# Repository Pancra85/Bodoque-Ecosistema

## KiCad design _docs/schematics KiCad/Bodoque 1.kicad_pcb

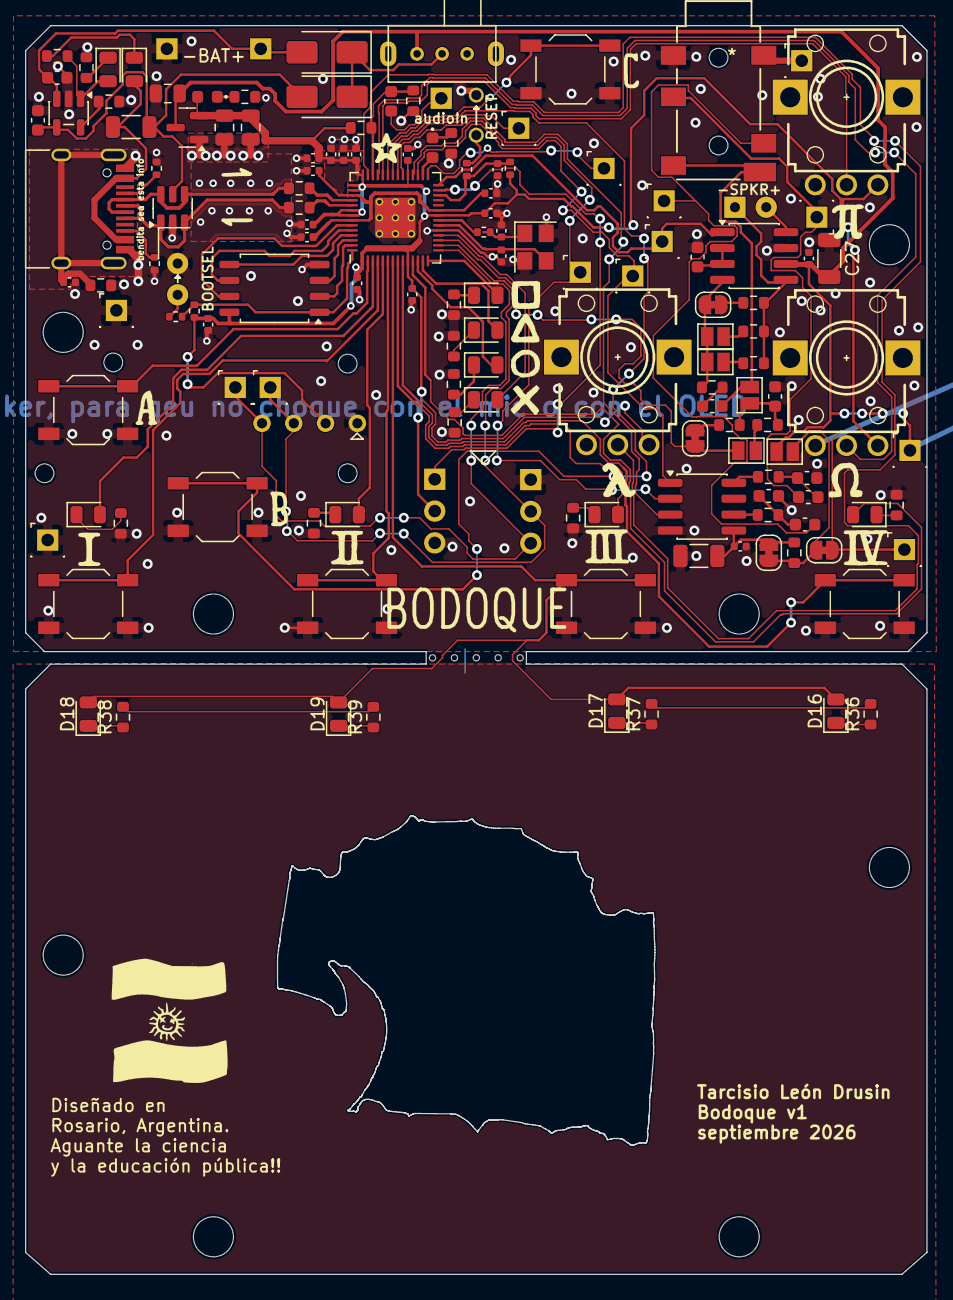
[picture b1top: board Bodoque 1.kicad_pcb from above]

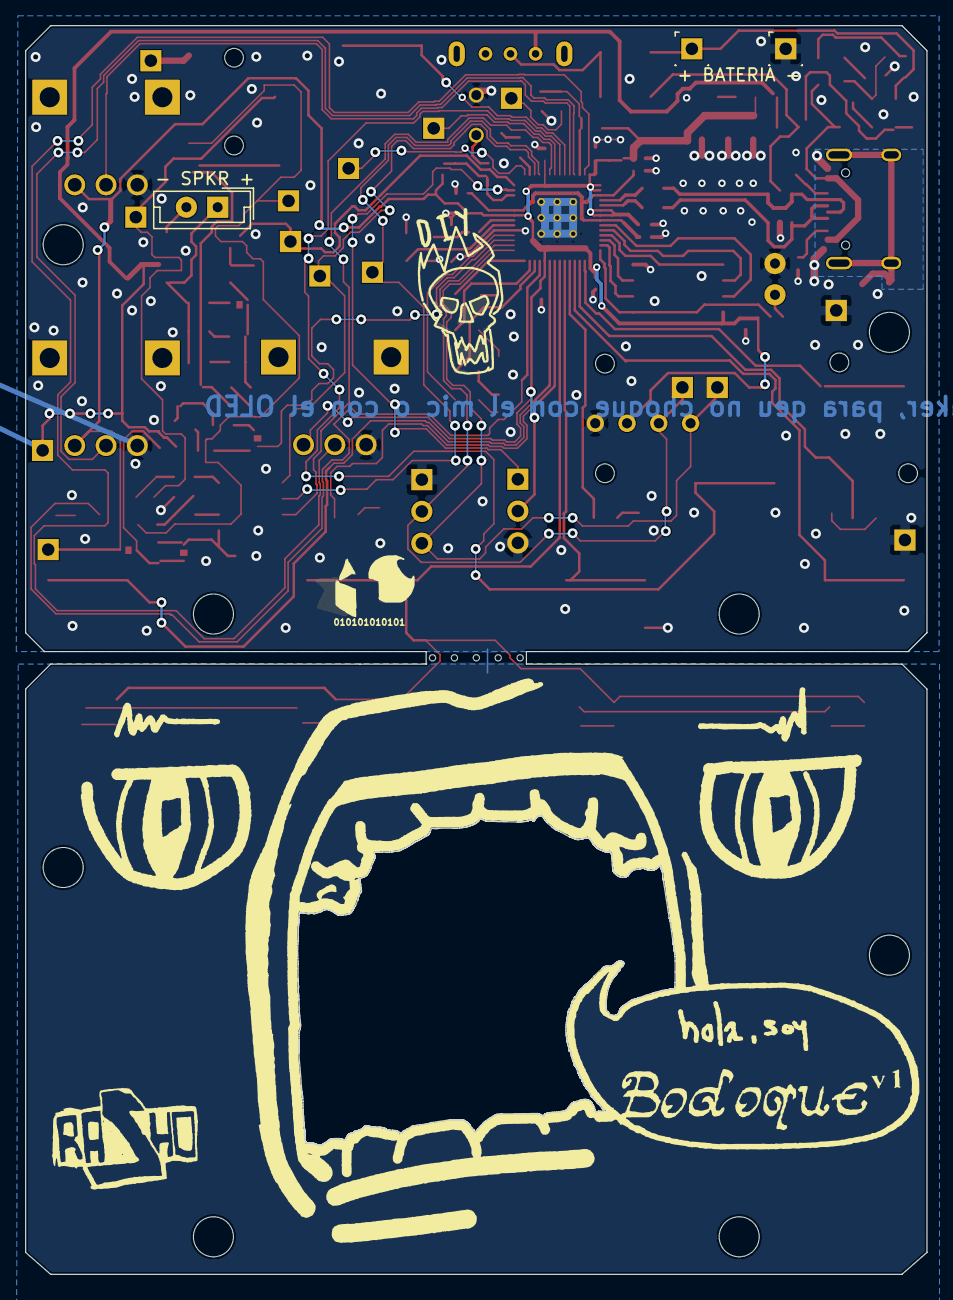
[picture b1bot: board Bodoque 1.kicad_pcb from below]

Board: 2 copper layers, 72.0 x 99.8 mm, 155 parts (3 on the bottom side), 99 nets.

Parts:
C1, C5, C6, C9, C10, C11, C12, C13, C14, C15, C18, C26, C28, C32: 100n; C_0402_1005Metric
C2, C3: 22pF; C_0402_1005Metric
C4, C8, C19: 1uF; C_0402_1005Metric
C7, C16, C17: 4.7uF; C_0805_2012Metric
C20, C21: 4.7u; C_0603_1608Metric
C22, C34, C35: 10u; C_0603_1608Metric
C24, C25, C29, C36, C37: 100n; C_0603_1608Metric
C27: 100u; C_1206_3216Metric
C33: 47u; C_1206_3216Metric
D1: SRV05-4; SOT-23-6
D2: POWER; LED_0603_1608Metric_Dot
D3, D4, D7, D8, D9, D10, D11, D12, D13, D14, D16, D17, D18, D19: LED; LED_0805_2012Metric
D5, D6: SS14; D_SMA
D15: LED; LED_0603_1608Metric_Dot
H3, H3#2, H3#3, H3#4, H3#5, H3#6, H3#7, H3#8, H3#9, H3#10, H3#11, H3#12: MountingHole; MountingHole_3.2mm_M3_ISO14580
J1: USB_C_Receptacle_USB2.0; USB_C_Receptacle_HRO_TYPE-C-31-M-12
J2: PJ-342 141; PJ-342B-TX-SMT_XKB
JP1, JP2, JP4, JP6, JP12: SolderJumper-2_P1.3mm_Open_Pad1.0x1.5mm
JP3, JP5, JP7: SolderJumper-2_P1.3mm_Bridged_RoundedPad1.0x1.5mm
JP8: CORTAR!; SolderJumper-2_P1.3mm_Bridged_RoundedPad1.0x1.5mm
MIC1: INMP441
OL1: OLED
R1, R7, R9: 1k; R_0402_1005Metric
R2, R11, R15, R17, R18, R19, R23, R24, R28, R29, R35: 4.7k; R_0603_1608Metric
R3, R4, R10, R12: 5k1; R_0402_1005Metric
R5, R6: 22R; R_0603_1608Metric
R8: 0R; R_1206_3216Metric
R13: 3.3k; R_0603_1608Metric
R14: 5.1k; R_0603_1608Metric
R16, R26: 100k; R_0603_1608Metric
R20: 30k; R_0603_1608Metric
R21, R30: 20k; R_0603_1608Metric
R22, R25: 10k; R_0603_1608Metric
R27: 10; R_0603_1608Metric
R31: 270; R_0603_1608Metric
R32, R33: 100; R_0603_1608Metric
R34: 1k; R_0603_1608Metric
R36, R37, R38, R39: 2.2k; R_0603_1608Metric
RV1, RV2, RV3: R_Potentiometer; Alpha 9mm vertical pot
SW1: BOOTSEL; JST_EH_B2B-EH-A_1x02_P2.50mm_Vertical small
SW2: RESET; JST_EH_B2B-EH-A_1x02_P2.50mm_Vertical small
SW3, SW4, SW5, SW6, SW7, SW8, SW9: SW_MEC_5G; SW_SPST_TL3342
SW10: SW_SPDT; SK-12D07 mini Switch
TP1: Bat-; PinHeader_1x01_P2.54mm_Vertical with label
TP2: audioIn; PinHeader_1x01_P2.54mm_Vertical with label
TP3, TP6: GND; PinHeader_1x01_P2.54mm_Vertical with label
TP4: - SPKR +; JST_EH_B2B-EH-A_1x02_P2.50mm_Vertical small
TP5: SD; PinHeader_1x01_P2.54mm_Vertical with label
TP7: VSW; PinHeader_1x01_P2.54mm_Vertical with label
TP8: 3.3V; PinHeader_1x01_P2.54mm_Vertical with label
TP9: SDA; PinHeader_1x01_P2.54mm_Vertical with label
TP10: SCL; PinHeader_1x01_P2.54mm_Vertical with label
TP11: 18; PinHeader_1x01_P2.54mm_Vertical with label
TP12: 23; PinHeader_1x01_P2.54mm_Vertical with label
TP13: dacWS; PinHeader_1x01_P2.54mm_Vertical with label
TP14: dacBCK; PinHeader_1x01_P2.54mm_Vertical with label
TP16: micIn; PinHeader_1x01_P2.54mm_Vertical with label
TP25: Bat+; PinHeader_1x01_P2.54mm_Vertical with label
TP26: DACROut; PinHeader_1x01_P2.54mm_Vertical with label
TP27: DACLOut; PinHeader_1x01_P2.54mm_Vertical with label
U1: W25Q16JVSIQ; SOIC-8_5.23x5.23mm_P1.27mm
U2: RP2040; RP2040-QFN-56
U3: MCP73831-3-OT; SOT-23-5
U4: XC6206PxxxMR; SOT-23
U5: NS8002; SOP-8_3.76x4.96mm_P1.27mm
U6: PT8211; SOP-8_3.76x4.96mm_P1.27mm
X1: 12MHz; Crystal_SMD_3225-4Pin_3.2x2.5mm

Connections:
+1V1: C4.2, C5.1, C6.1, U2.23 (DVDD), U2.45 (VREG_VOUT), U2.50 (DVDD)
+3V3: C1.1, C7.1, C8.1, C9.1, C10.1, C11.1, C12.1, C13.1, C14.1, C15.1, C17.1, C18.1, D2.2, JP3.2 (B), MIC1.2 (VDD), OL1.3 (VCC), R10.2, R12.2, R16.1, RV1.3, RV2.3, RV3.3, TP8.1 (1_1), U1.8 (VCC), U2.1 (IOVDD), U2.10 (IOVDD), U2.22 (IOVDD), U2.33 (IOVDD), U2.42 (IOVDD), U2.43 (ADC_AVDD), U2.44 (VREG_VIN), U2.48 (USB_VDD), U2.49 (IOVDD), U4.2 (VO)
+5V: C20.2, D1.5 (VP), D5.2 (A), R8.2, U3.4 (V_{DD})
+BATT: C21.2, D6.2 (A), TP25.1 (1_1), U3.3 (V_{BAT})
+VSW: C16.1, C26.2, C27.2, JP2.2 (B), SW10.3 (C), TP7.1 (1_1), U4.3 (VI), U5.6 (VCC)
/441SCK: MIC1.6 (SCK), OL1.1 (SDA), TP9.1 (1_1), U2.15 (GPIO12)
/441SD: MIC1.1 (SD), U2.27 (GPIO16)
/441WS: MIC1.5 (WS), OL1.2 (SCL), TP10.1 (1_1), U2.16 (GPIO13)
/CS: R1.1, R12.1, U1.1 (~CS), U2.56 (QSPI_SS_N)
/DACLOut: C35.2, J2.4, TP27.1 (1_1)
/DACLOutSwitch: C24.2, J2.5, J2.6, JP12.2 (B)
/DACROut: C34.2, J2.3, TP26.1 (1_1)
/GPIO0: SW8.1, U2.2 (GPIO0)
/GPIO1: D7.2 (A), U2.3 (GPIO1)
/GPIO2: SW6.1, U2.4 (GPIO2)
/GPIO3: D8.2 (A), U2.5 (GPIO3)
/GPIO4: SW3.1, U2.6 (GPIO4)
/GPIO5: D16.2 (A), D17.2 (A), D18.2 (A), D19.2 (A), SW4.1, U2.7 (GPIO5)
/GPIO6: D9.2 (A), U2.8 (GPIO6)
/GPIO7: SW5.1, U2.9 (GPIO7)
/GPIO8: D10.2 (A), U2.11 (GPIO8)
/GPIO9: D11.2 (A), U2.12 (GPIO9)
/GPIO10: D12.2 (A), U2.13 (GPIO10)
/GPIO11: D13.2 (A), U2.14 (GPIO11)
/GPIO14: JP4.1 (A), JP5.1 (A), U2.17 (GPIO14)
/GPIO15: D14.2 (A), U2.18 (GPIO15)
/GPIO17: TP5.1 (1_1), U2.28 (GPIO17), U5.1 (SD)
/GPIO18: TP11.1 (1_1), U2.29 (GPIO18)
/GPIO19: D15.2, U2.30 (GPIO19)
/GPIO20: TP14.1 (1_1), U2.31 (GPIO20), U6.1 (BCK)
/GPIO21: TP13.1 (1_1), U2.32 (GPIO21), U6.2 (WS)
/GPIO22: U2.34 (GPIO22), U6.3 (DIN)
/GPIO23: TP12.1 (1_1), U2.35 (GPIO23)
/GPIO24: SW9.1, U2.36 (GPIO24)
/GPIO25: SW7.1, U2.37 (GPIO25)
/GPIO26/ADC0: RV1.2, U2.38 (GPIO26/ADC0)
/GPIO27/ADC1: RV2.2, U2.39 (GPIO27/ADC1)
/GPIO28/ADC2: C22.1, R16.2, R26.1, U2.40 (GPIO28/ADC2)
/GPIO29/ADC3: RV3.2, U2.41 (GPIO29/ADC3)
/RP2040/QSPI_CLK: U1.6 (CLK), U2.52 (QSPI_SCLK)
/RP2040/SD0: U1.5 (DI(IO0)), U2.53 (QSPI_SD0)
/RP2040/SD1: U1.2 (DO(IO1)), U2.55 (QSPI_SD1)
/RP2040/SD2: U1.3 (IO2), U2.54 (QSPI_SD2)
/RP2040/SD3: U1.7 (IO3), U2.51 (QSPI_SD3)
/RP2040/USB_DT+: R5.2, U2.47 (D+)
/RP2040/USB_DT-: R6.2, U2.46 (D-)
/USBC/CC1: J1.A5 (CC1), R3.1
/USBC/CC2: J1.B5 (CC2), R4.1
/USB_D+: D1.1 (L1), D1.3 (L2), J1.A6 (D+), J1.B6 (D+), R5.1
/USB_D-: D1.4 (L3), D1.6 (L4), J1.A7 (D-), J1.B7 (D-), R6.1
/~RESET: C19.1, R9.1, R10.1, U2.26 (~RUN)
GND: C1.2, C2.1, C3.1, C4.1, C5.2, C6.2, C7.2, C8.2, C9.2, C10.2, C11.2, C12.2, C13.2, C14.2, C15.2, C16.2, C17.2, C18.2, C19.2, C20.1, C21.1, C25.2, C26.1, C27.1, C28.2, C29.1, C32.1, C33.2, C36.1, C37.1, D1.2 (VN), J1.A1 (GND), J1.A12 (GND), J1.B1 (GND), J1.B12 (GND), J2.1, MIC1.3 (GND), MIC1.4 (L/R), OL1.4 (GND), R2.2, R3.2, R4.2, R11.2, R13.2, R14.1, R17.2, R18.2, R19.2, R23.2, R24.2, R25.2, R26.2, R28.2, R29.2, R35.2, RV1.1, RV2.1, RV3.1, SW1.1, SW2.1, SW3.2, SW4.2, SW5.2, SW6.2, SW7.2, SW8.2, SW9.2, TP1.1 (1_1), TP3.1 (1_1), TP6.1 (1_1), U1.4 (GND), U2.19 (TESTEN), U2.57 (GND), U3.2 (V_{SS}), U4.1 (GND), U5.7 (GND), U6.4 (GND), X1.2, X1.4
unnamed: C3.2, R7.1, X1.1
unnamed: C22.2, TP2.1 (1_1)
unnamed: C24.1, R30.2
unnamed: C34.1, C36.2, R32.1
unnamed: C35.1, C37.2, R33.1
unnamed: D2.1, R2.1
unnamed: D3.2 (A), R15.2, U3.1 (STAT)
unnamed: D3.1 (K), R14.2
unnamed: D4.1 (K), R15.1
unnamed: D5.1 (K), D6.1 (K), SW10.2 (B)
unnamed: D7.1 (K), R18.1
unnamed: D8.1 (K), R19.1
unnamed: D9.1 (K), R23.1
unnamed: D10.1 (K), R24.1
unnamed: D11.1 (K), R11.1
unnamed: D12.1 (K), R28.1
unnamed: D13.1 (K), R29.1
unnamed: D14.1 (K), R17.1
unnamed: D15.1, R35.1
unnamed: D16.1 (K), R36.1
unnamed: D17.1 (K), R37.1
unnamed: D18.1 (K), R38.1
unnamed: D19.1 (K), R39.1
unnamed: C28.1, J1.S1 (SHIELD), R25.1
unnamed: J2.2, TP16.1 (1_1)
unnamed: JP1.1 (A), JP6.1 (A), JP7.1 (A), R30.1, U5.4 (-IN)
unnamed: JP1.2 (B), R22.2
unnamed: JP2.1 (A), JP3.1 (A), JP8.1 (A), R27.2
unnamed: JP4.2 (B), R31.2
unnamed: JP5.2 (B), R34.2
unnamed: JP6.2 (B), R20.2
unnamed: JP7.2 (B), R21.2
unnamed: C32.2, C33.1, JP8.2 (B), R27.1, U6.5 (VCC)
unnamed: C29.2, JP12.1 (A), R31.1, R34.1
unnamed: R1.2, SW1.2
unnamed: R9.2, SW2.2
unnamed: R36.2, R37.2
unnamed: R38.2, R39.2
unnamed: C2.2, U2.20 (XTAL_IN), X1.3
unnamed: R7.2, U2.21 (XTAL_OUT)
unnamed: R13.1, U3.5 (PROG)
unnamed: C25.1, U5.2 (BYP), U5.3 (+IN)
unnamed: R20.1, R21.1, R22.1, TP4.1, U5.5 (VO1)
unnamed: TP4.2, U5.8 (VO2)
unnamed: R33.2, U6.6 (LCH)
unnamed: R32.2, U6.8 (RCH)
VBUS: D4.2 (A), J1.A4 (VBUS), J1.A9 (VBUS), J1.B4 (VBUS), J1.B9 (VBUS), R8.1
